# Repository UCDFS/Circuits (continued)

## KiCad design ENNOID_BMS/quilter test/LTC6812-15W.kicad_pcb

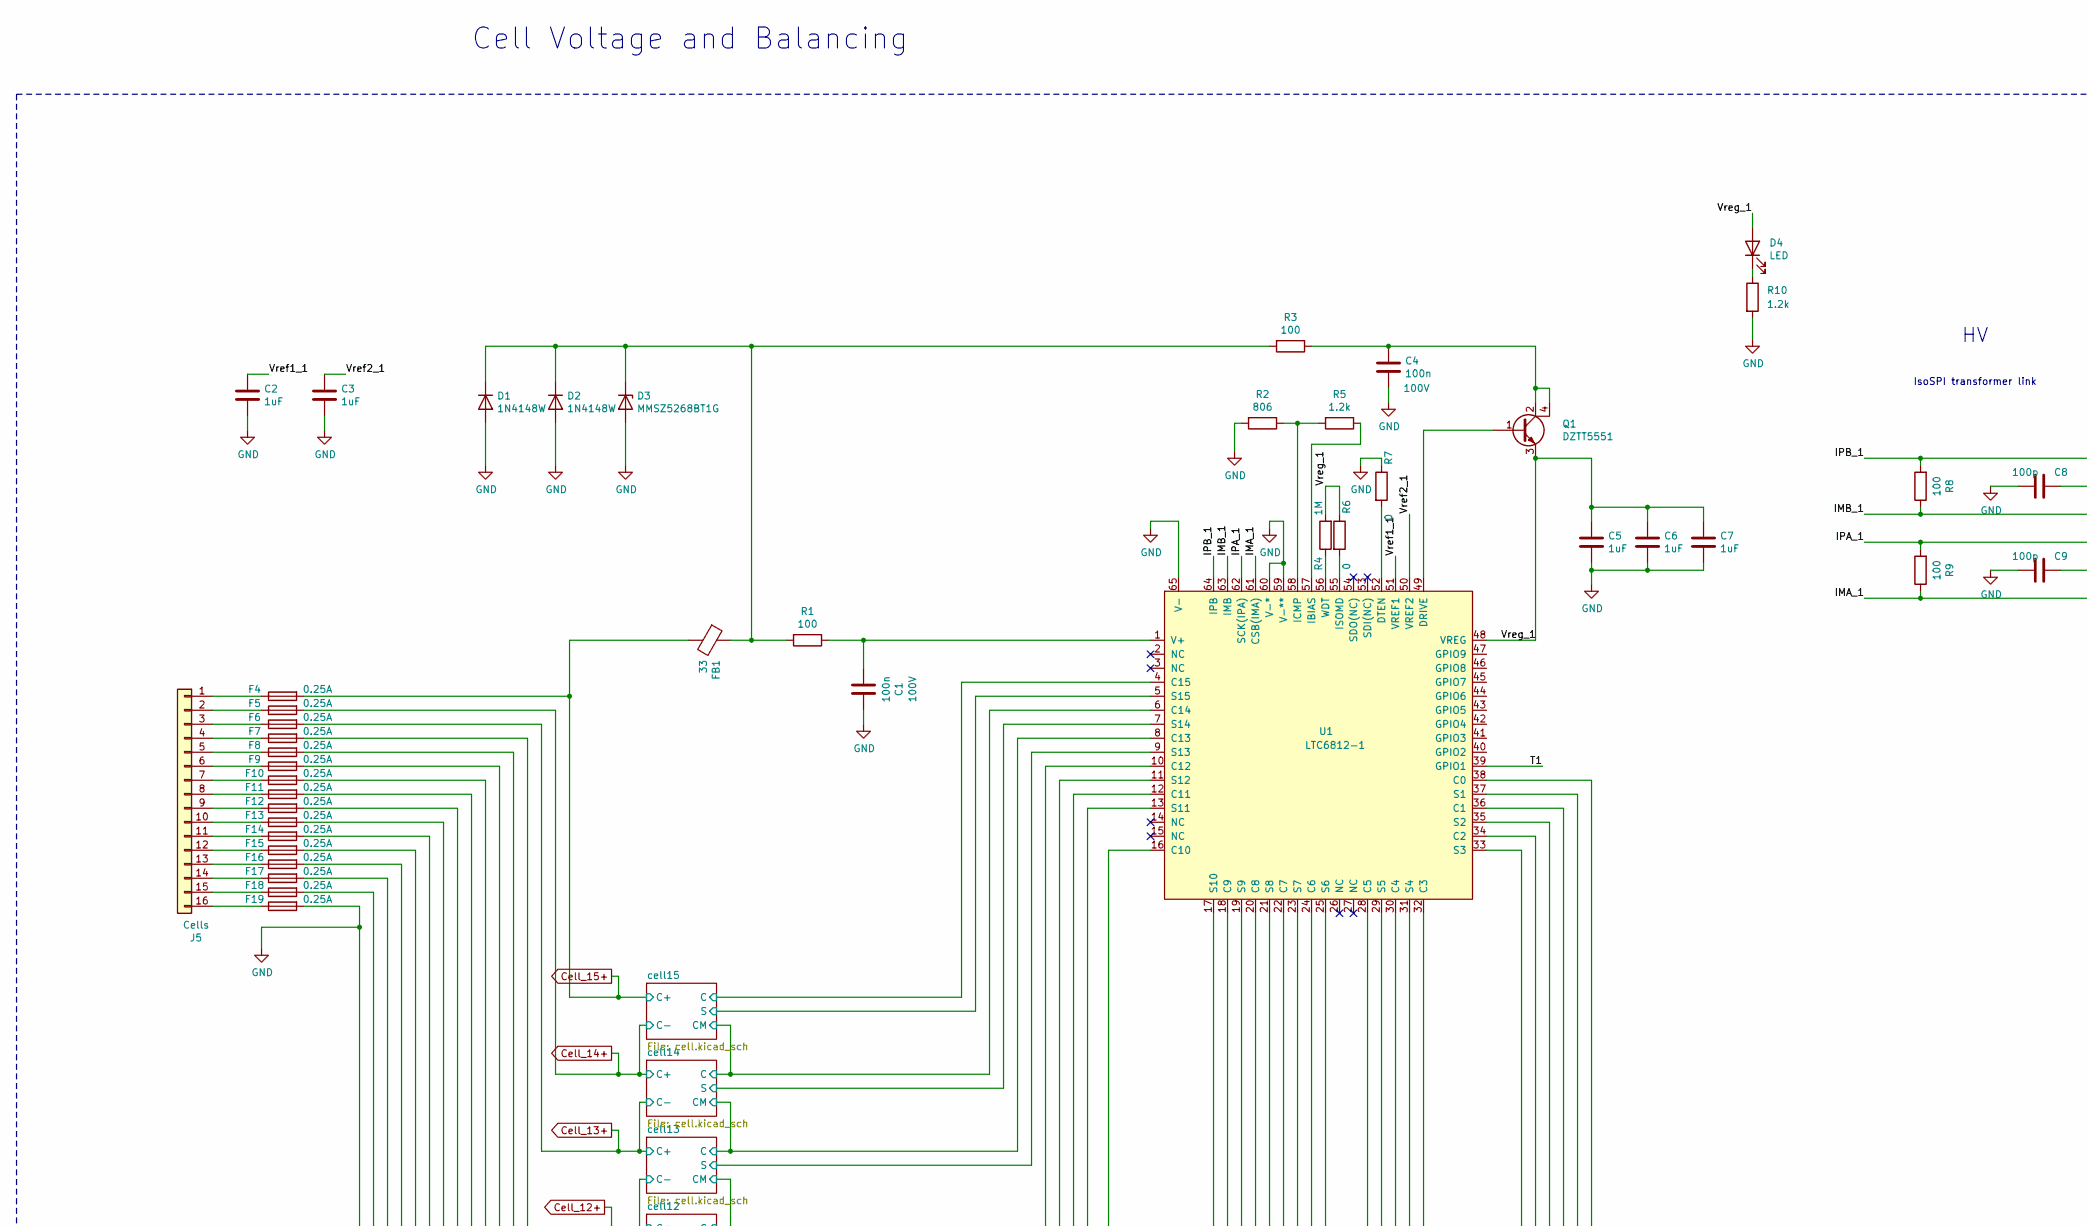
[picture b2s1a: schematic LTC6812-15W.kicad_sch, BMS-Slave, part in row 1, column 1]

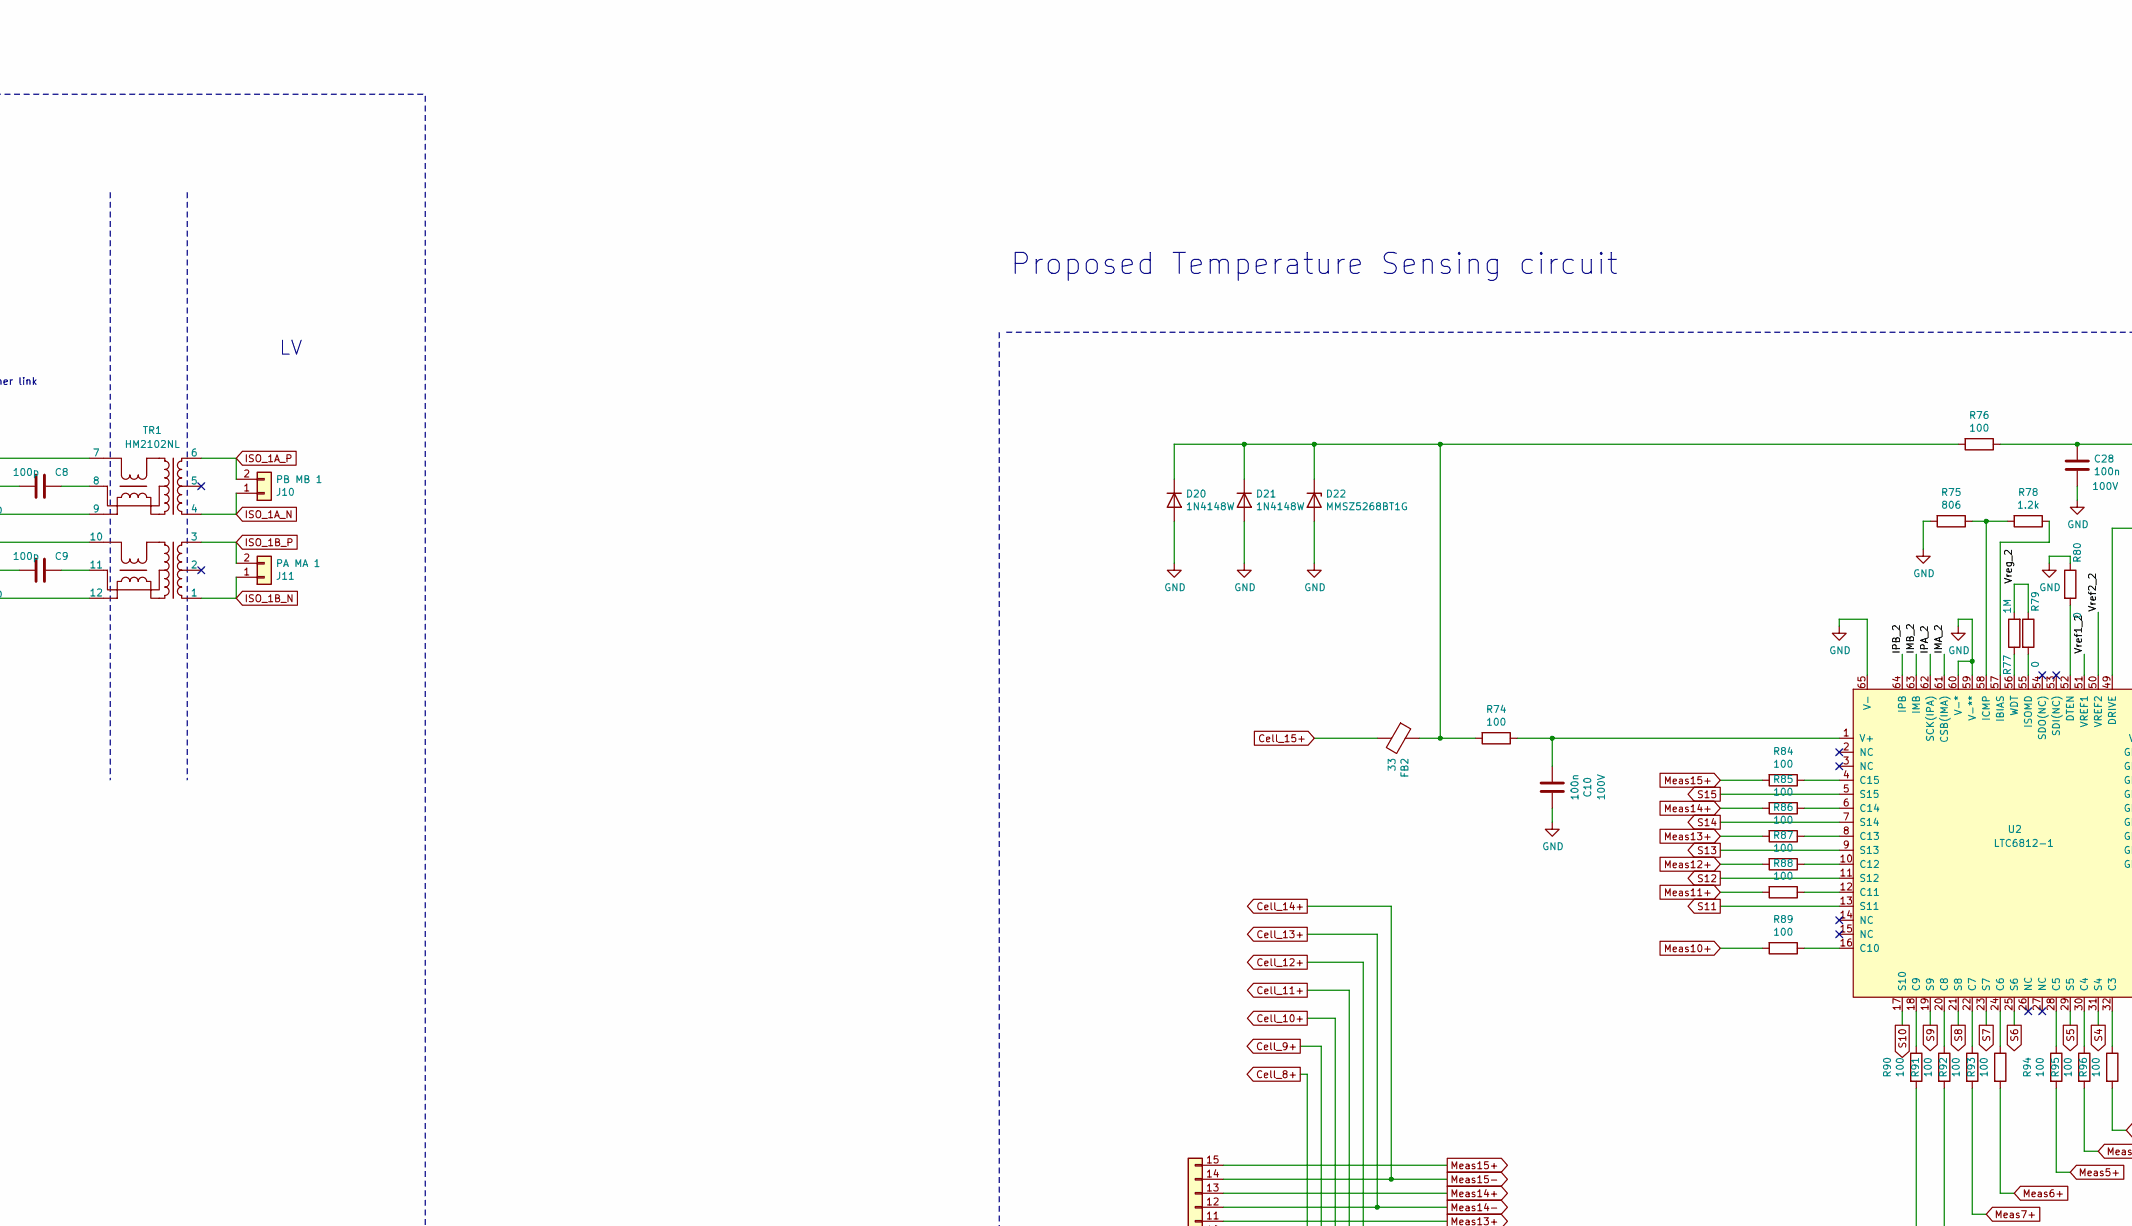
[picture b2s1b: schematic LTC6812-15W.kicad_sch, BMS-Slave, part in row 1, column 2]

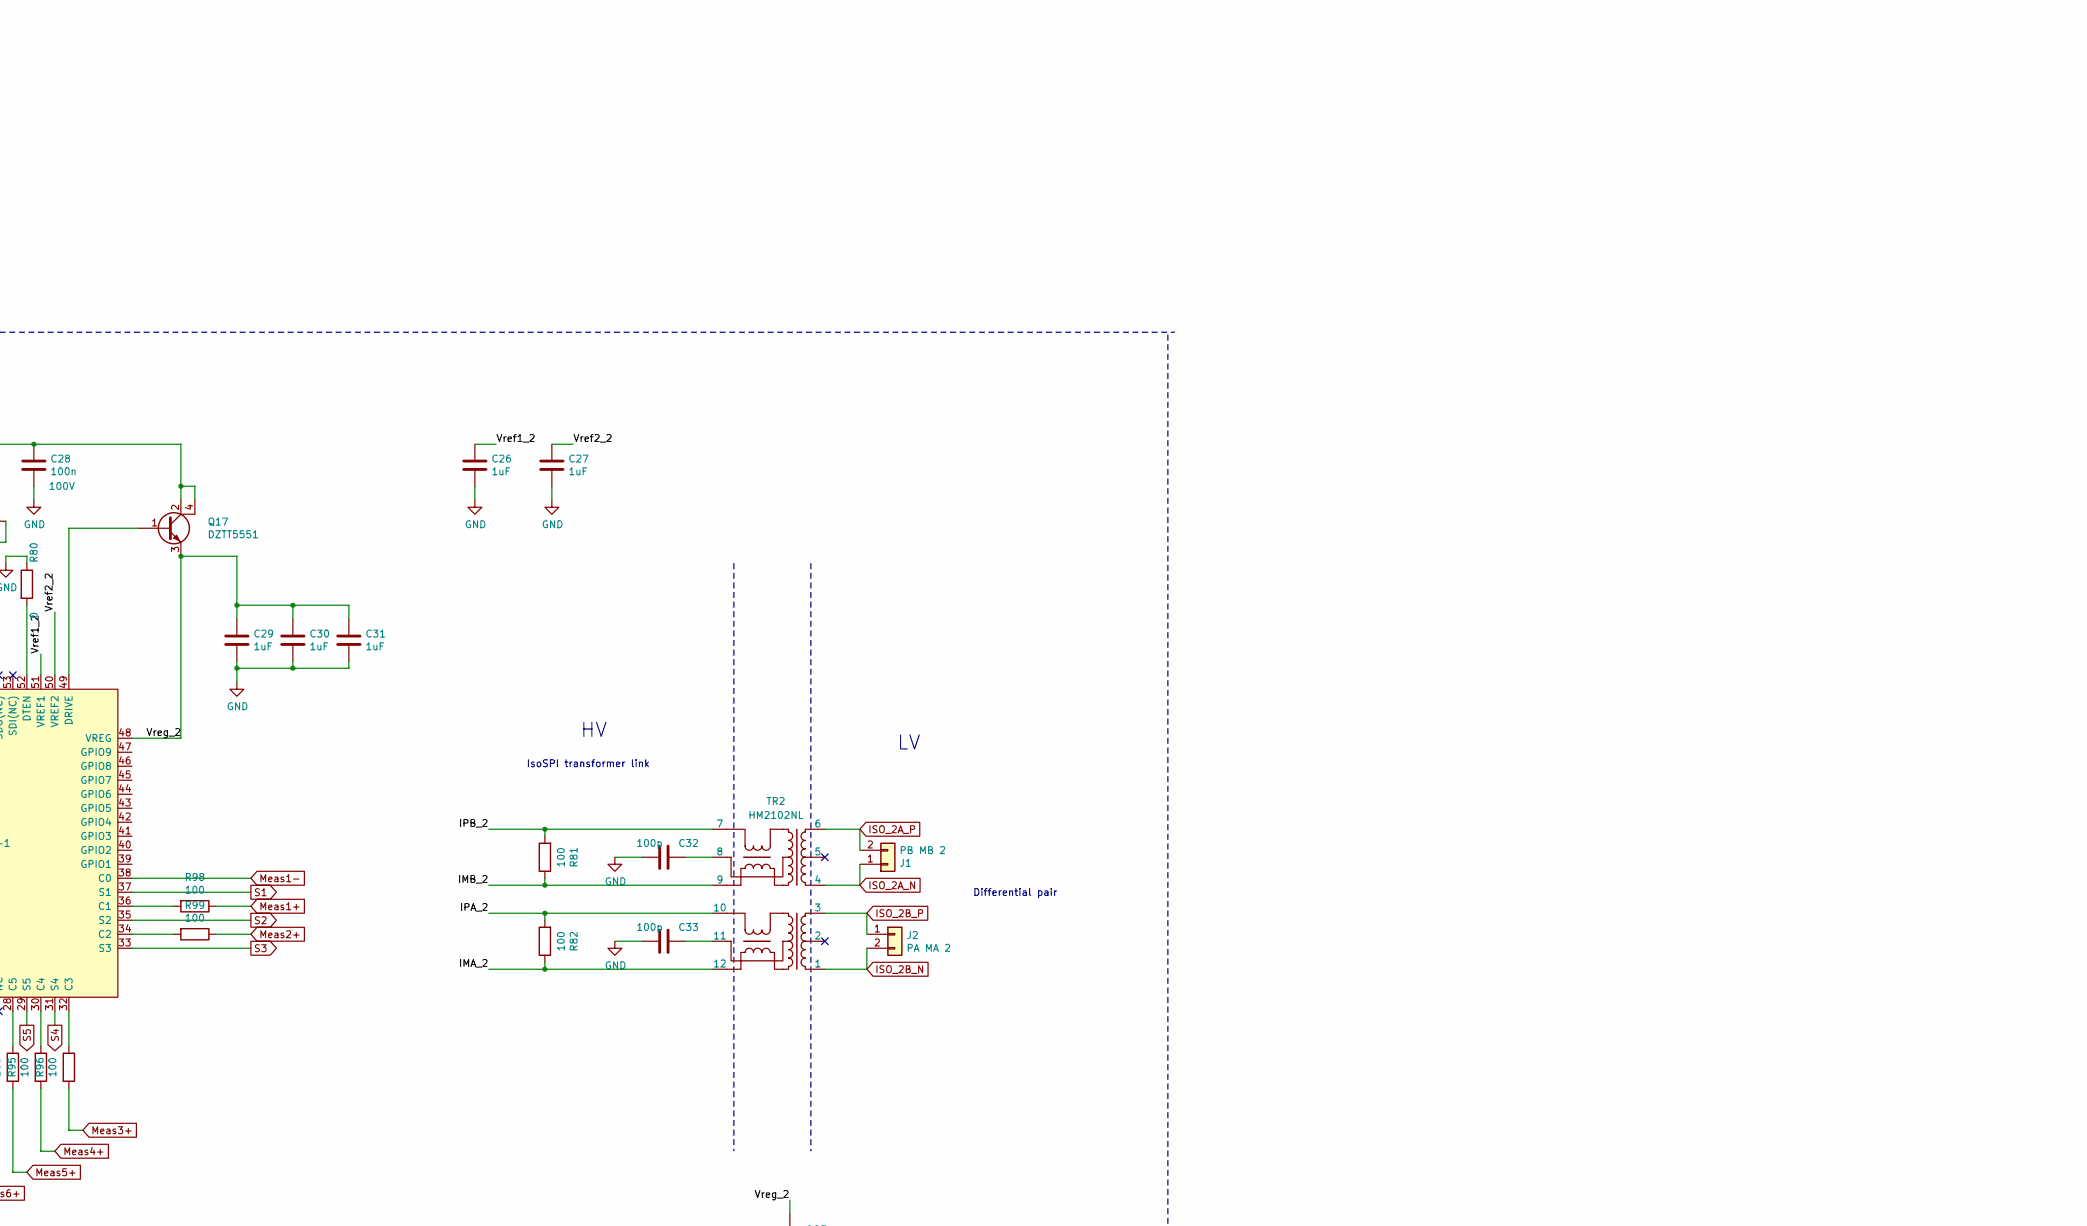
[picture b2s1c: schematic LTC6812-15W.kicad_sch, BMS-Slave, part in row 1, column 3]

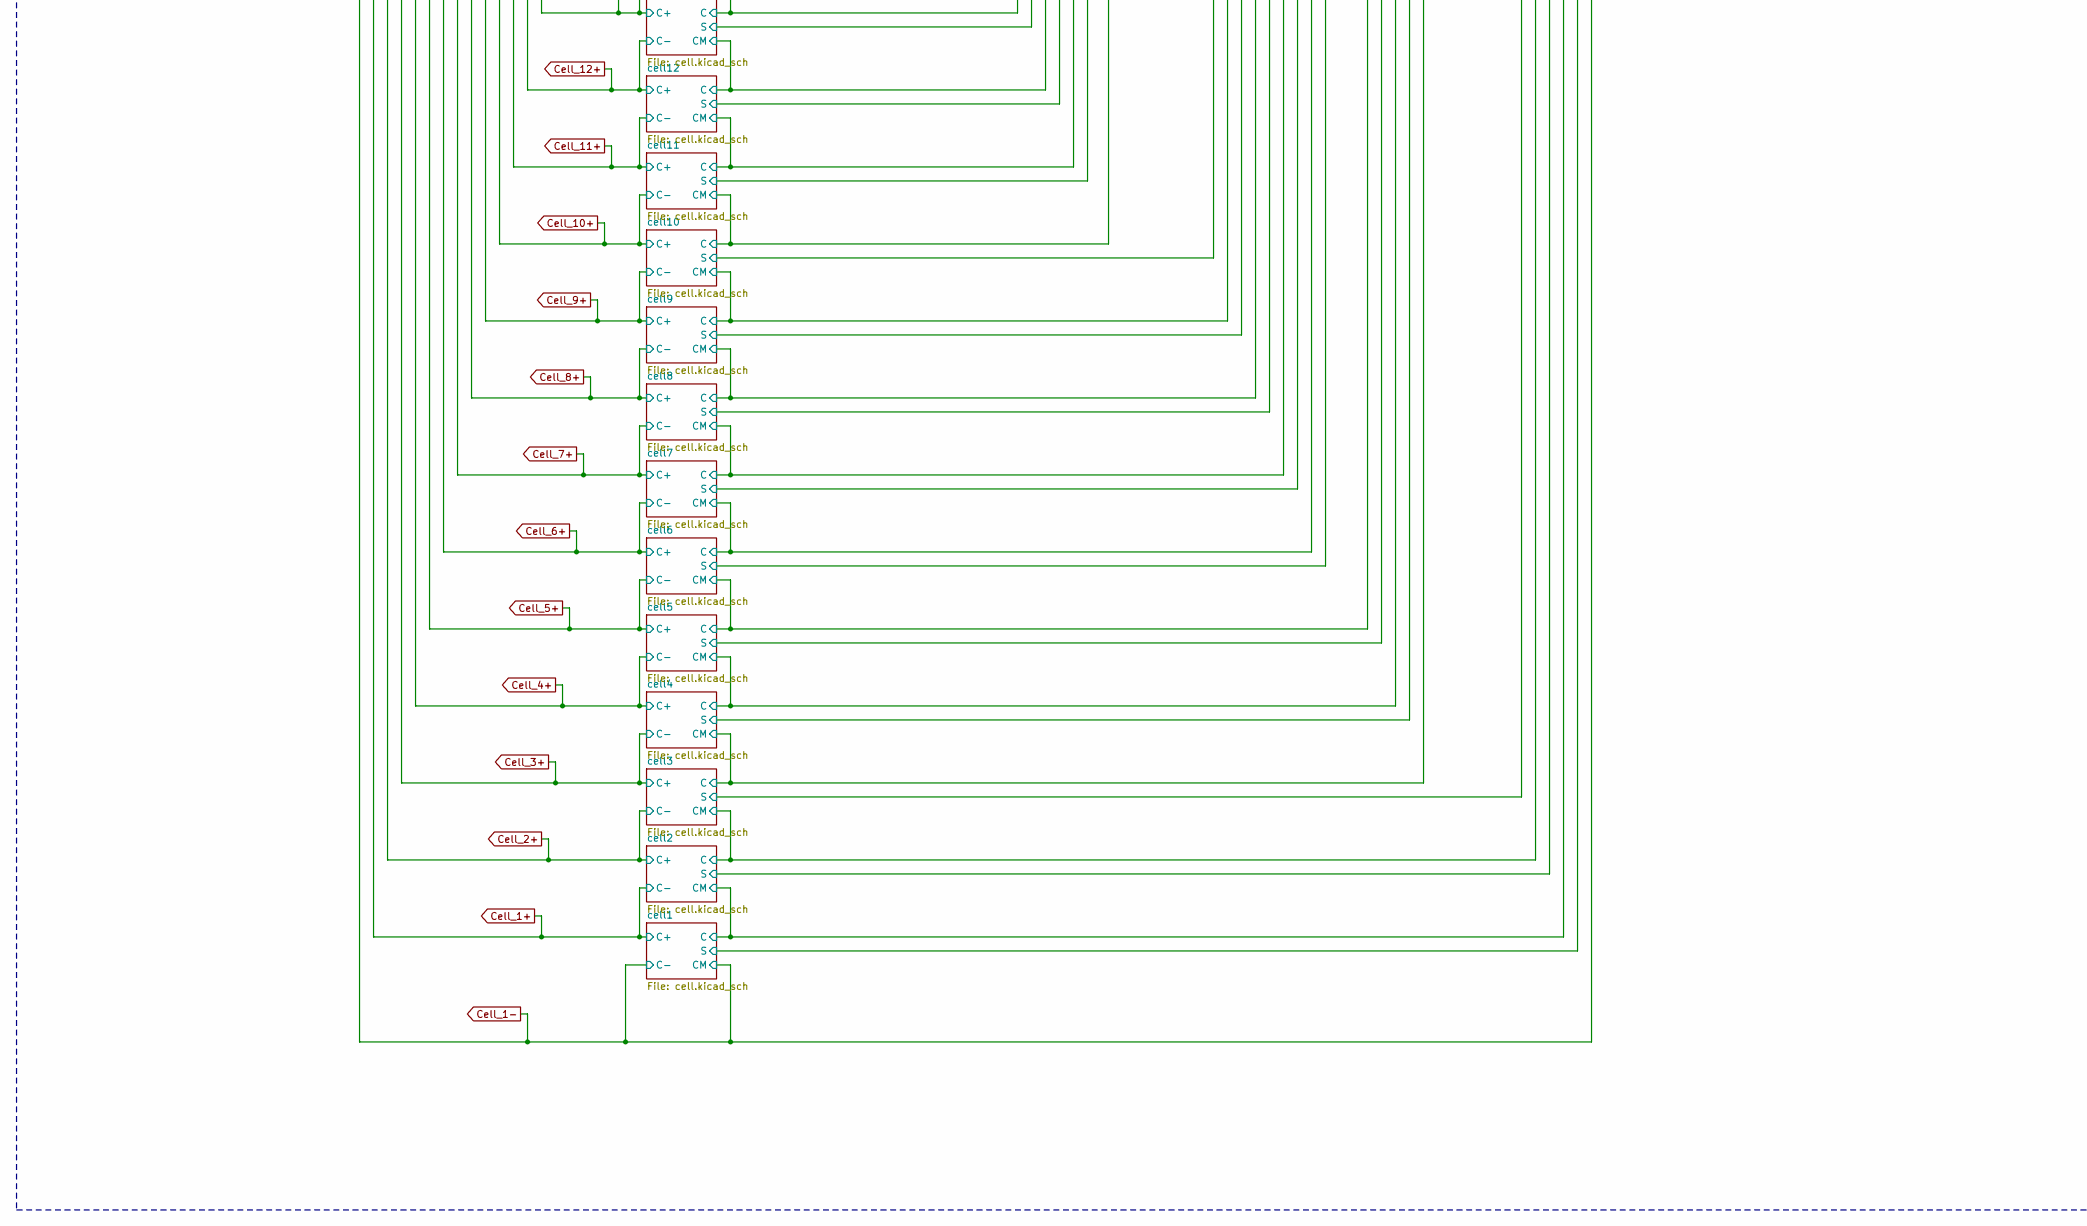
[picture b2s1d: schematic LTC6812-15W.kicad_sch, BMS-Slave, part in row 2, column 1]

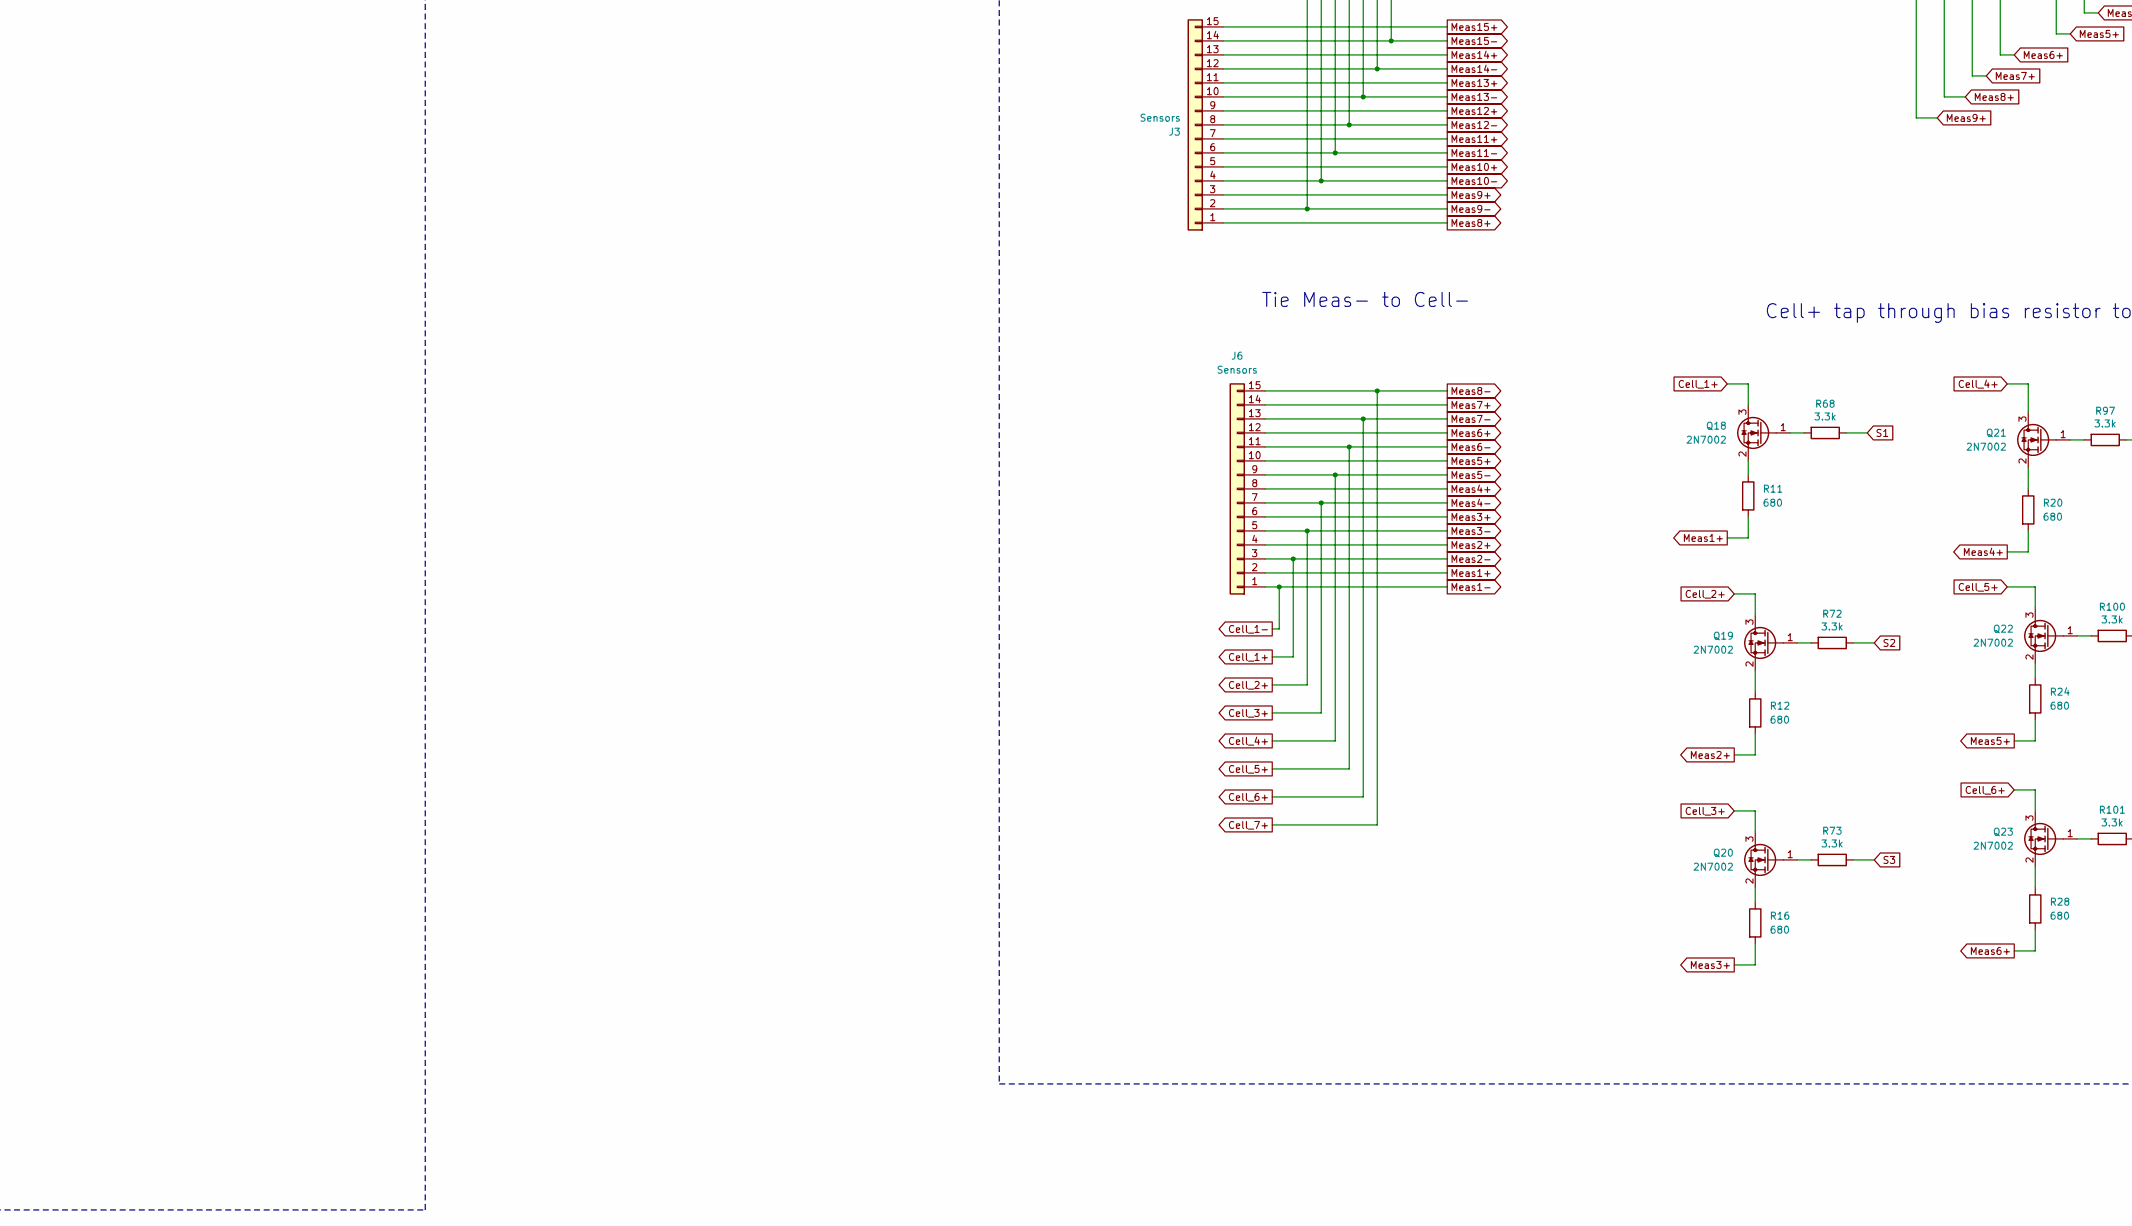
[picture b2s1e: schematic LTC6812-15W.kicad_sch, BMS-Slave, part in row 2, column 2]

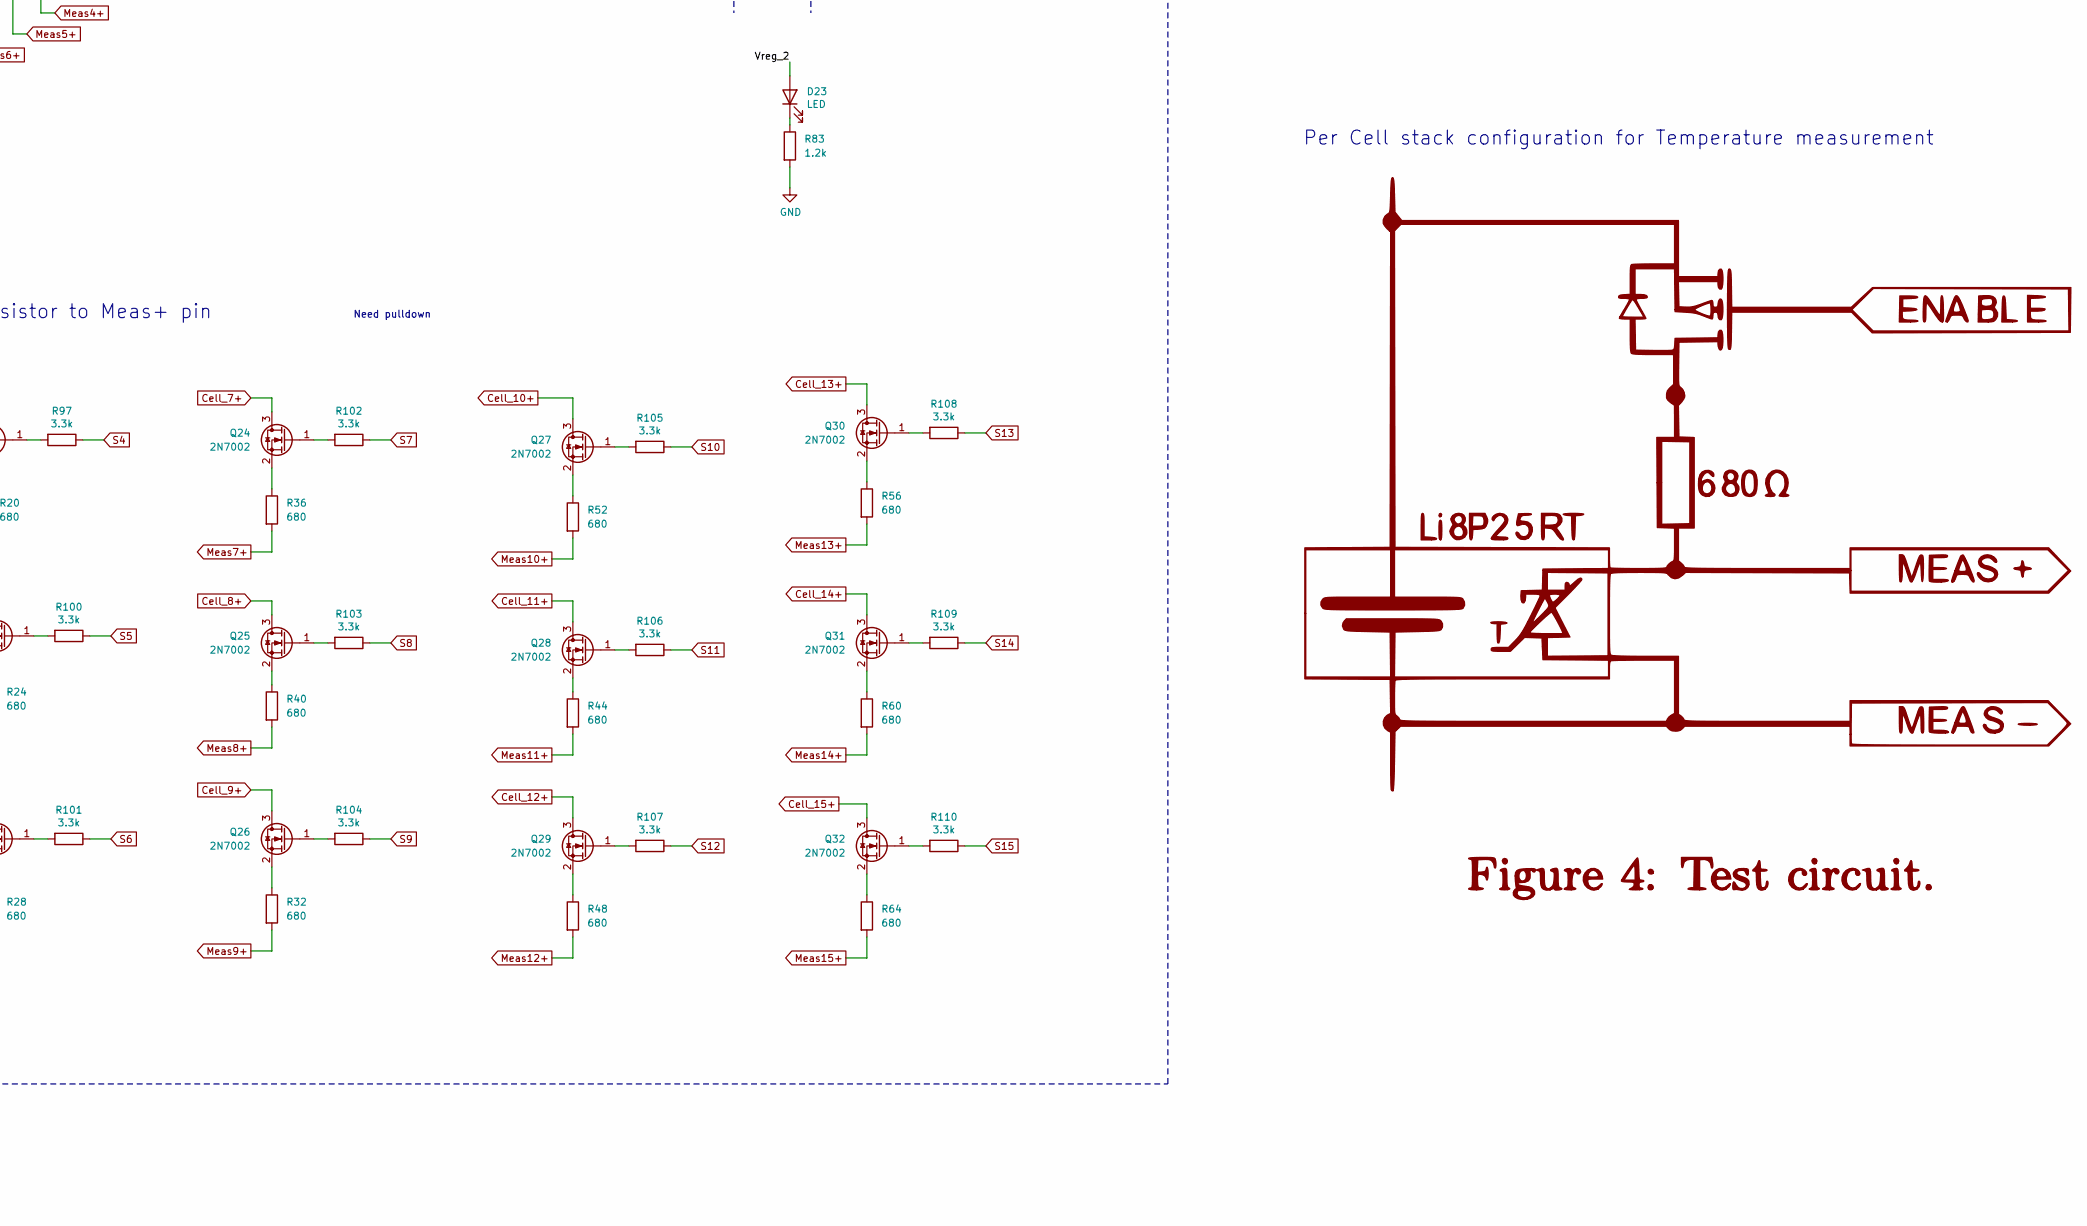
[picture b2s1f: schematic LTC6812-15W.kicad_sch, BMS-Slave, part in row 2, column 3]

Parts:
C1, C4, C10, C28: 100n; C_0603_1608Metric; Voltage 100V; Part Number GRM188R72A104KA35D
C2, C3, C5, C6, C7, C26, C27, C29, C30, C31: 1uF; C_0603_1608Metric; Part Number CL10B105KP8NNNC
C8, C9, C32, C33: 100p; C_0603_1608Metric; Part Number GRM1885C1H101JA01D
D1, D2, D20, D21: 1N4148W; D_SOD-123; Part Number 1N4148W-7-F
D3, D22: MMSZ5268BT1G; D_SOD-123; Part Number MMSZ5268BT1G
D4, D23: LED; LED_0603_1608Metric_Pad1.05x0.95mm_HandSolder; Part Number VLMTG1400-GS08
F4, F5, F6, F7, F8, F9, F10, F11, F12, F13, F14, F15, F16, F17, F18, F19: 0.25A; Fuse_0603_1608Metric; Part Number 0438.250WR
FB1, FB2: 33; R_0603_1608Metric; Part Number BLM18PG330SN1D
J1: PB MB 2; JST_XH_B2B-XH-A_1x02_P2.50mm_Vertical; Part Number B2B-XH-A
J2: PA MA 2; JST_XH_B2B-XH-A_1x02_P2.50mm_Vertical; Part Number B2B-XH-A
J3, J6: Sensors; JST_XH_S15B-XH-A_1x15_P2.50mm_Horizontal; Part Number S15B-XH-A(LF)(SN)
J5: Cells; JST_XH_S16B-XH-A_1x16_P2.50mm_Horizontal; Part Number S16B-XH-A(LF)(SN)
J10: PB MB 1; JST_XH_B2B-XH-A_1x02_P2.50mm_Vertical; Part Number B2B-XH-A
J11: PA MA 1; JST_XH_B2B-XH-A_1x02_P2.50mm_Vertical; Part Number B2B-XH-A
Q1, Q17: DZTT5551; SOT-223; Part Number DZT5551-13
Q18, Q19, Q20, Q21, Q22, Q23, Q24, Q25, Q26, Q27, Q28, Q29, Q30, Q31, Q32: 2N7002; SOT-23
R1, R3, R8, R9, R74, R76, R81, R82, R84, R85, R86, R87, R88, R89, R90, R91, R92, R93, R94, R95, R96, R98, R99: 100; R_0603_1608Metric; Part Number CRCW0603100RFKEA
R2, R75: 806; R_0603_1608Metric; Part Number CRCW0603806RFKEA
R4, R77: 1M; R_0603_1608Metric; Part Number CRCW06031M00FKEA
R5, R10, R78, R83: 1.2k; R_0603_1608Metric; Part Number CRCW06031K20FKEA
R6, R7, R79, R80: 0; R_0603_1608Metric; Part Number CRCW06030000Z0EA
R11, R12, R16, R20, R24, R28, R32, R36, R40, R44, R48, R52, R56, R60, R64: 680; R_0603_1608Metric; Part Number CRCW0603680RFKEA
R68, R72, R73, R97, R100, R101, R102, R103, R104, R105, R106, R107, R108, R109, R110: 3.3k; R_0603_1608Metric; Part Number CRCW06033K30FKEA
TR1, TR2: HM2102NL; Part Number HM2102NL
U1, U2: LTC6812-1; TQFP-64-1EP_10x10mm_P0.5mm_EP8x8mm; Part Number LTC6812-1

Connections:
/IMA_1: R9.1, TR1.12, U1.61 (CSB(IMA))
/IMA_2: R82.1, TR2.12, U2.61 (CSB(IMA))
/IMB_1: R8.1, TR1.9, U1.63 (IMB)
/IMB_2: R81.1, TR2.9, U2.63 (IMB)
/IPA_1: R9.2, TR1.10, U1.62 (SCK(IPA))
/IPA_2: R82.2, TR2.10, U2.62 (SCK(IPA))
/IPB_1: R8.2, TR1.7, U1.64 (IPB)
/IPB_2: R81.2, TR2.7, U2.64 (IPB)
/T1: U1.39 (GPIO1)
/Vref1_1: C2.2, U1.51 (VREF1)
/Vref1_2: C26.2, U2.51 (VREF1)
/Vref2_1: C3.2, U1.50 (VREF2)
/Vref2_2: C27.2, U2.50 (VREF2)
/Vreg_1: C5.2, C6.2, C7.2, D4.2 (A), Q1.3 (E), R4.2, R6.1, U1.48 (VREG)
/Vreg_2: C29.2, C30.2, C31.2, D23.2 (A), Q17.3 (E), R77.2, R79.1, U2.48 (VREG)
/cell1/C: U1.36 (C1); also elsewhere on the board
/cell1/S: U1.37 (S1); also elsewhere on the board
/cell2/C: U1.34 (C2); also elsewhere on the board
/cell2/S: U1.35 (S2); also elsewhere on the board
/cell3/C: U1.32 (C3); also elsewhere on the board
/cell3/S: U1.33 (S3); also elsewhere on the board
/cell4/C: U1.30 (C4); also elsewhere on the board
/cell4/S: U1.31 (S4); also elsewhere on the board
/cell5/C: U1.28 (C5); also elsewhere on the board
/cell5/S: U1.29 (S5); also elsewhere on the board
/cell6/C: U1.24 (C6); also elsewhere on the board
/cell6/S: U1.25 (S6); also elsewhere on the board
/cell7/C: U1.22 (C7); also elsewhere on the board
/cell7/S: U1.23 (S7); also elsewhere on the board
/cell8/C: U1.20 (C8); also elsewhere on the board
/cell8/S: U1.21 (S8); also elsewhere on the board
/cell9/S: U1.19 (S9); also elsewhere on the board
/cell10/C: U1.16 (C10); also elsewhere on the board
/cell10/CM: U1.18 (C9); also elsewhere on the board
/cell10/S: U1.17 (S10); also elsewhere on the board
/cell11/C: U1.12 (C11); also elsewhere on the board
/cell11/S: U1.13 (S11); also elsewhere on the board
/cell12/C: U1.10 (C12); also elsewhere on the board
/cell12/S: U1.11 (S12); also elsewhere on the board
/cell13/C: U1.8 (C13); also elsewhere on the board
/cell13/S: U1.9 (S13); also elsewhere on the board
/cell14/C: U1.6 (C14); also elsewhere on the board
/cell14/S: U1.7 (S14); also elsewhere on the board
/cell15/C: U1.4 (C15); also elsewhere on the board
/cell15/S: U1.5 (S15); also elsewhere on the board
Cell_1+: F18.2, J6.3, Q18.3 (D); also elsewhere on the board
Cell_1-: C1.1, C2.1, C3.1, C4.1, C5.1, C6.1, C7.1, C8.1, C9.1, C10.1, C26.1, C27.1, C28.1, C29.1, C30.1, C31.1, C32.1, C33.1, D1.2 (A), D2.2 (A), D3.2 (A), D20.2 (A), D21.2 (A), D22.2 (A), F19.2, J6.1, R2.2, R7.1, R10.2, R75.2, R80.1, R83.2, U1.38 (C0), U1.59 (V-**), U1.60 (V-*), U1.65 (V-), U2.38 (C0), U2.59 (V-**), U2.60 (V-*), U2.65 (V-); also elsewhere on the board
Cell_2+: F17.2, J6.5, Q19.3 (D); also elsewhere on the board
Cell_3+: F16.2, J6.7, Q20.3 (D); also elsewhere on the board
Cell_4+: F15.2, J6.9, Q21.3 (D); also elsewhere on the board
Cell_5+: F14.2, J6.11, Q22.3 (D); also elsewhere on the board
Cell_6+: F13.2, J6.13, Q23.3 (D); also elsewhere on the board
Cell_7+: F12.2, J6.15, Q24.3 (D); also elsewhere on the board
Cell_8+: F11.2, J3.2, Q25.3 (D); also elsewhere on the board
Cell_9+: F10.2, J3.4, Q26.3 (D); also elsewhere on the board
Cell_10+: F9.2, J3.6, Q27.3 (D); also elsewhere on the board
Cell_11+: F8.2, J3.8, Q28.3 (D); also elsewhere on the board
Cell_12+: F7.2, J3.10, Q29.3 (D); also elsewhere on the board
Cell_13+: F6.2, J3.12, Q30.3 (D); also elsewhere on the board
Cell_14+: F5.2, J3.14, Q31.3 (D); also elsewhere on the board
Cell_15+: F4.2, FB1.2, FB2.2, Q32.3 (D); also elsewhere on the board
ISO_1A_N: J10.1, TR1.4
ISO_1A_P: J10.2, TR1.6
ISO_1B_N: J11.1, TR1.1
ISO_1B_P: J11.2, TR1.3
ISO_2A_N: J1.1, TR2.4
ISO_2A_P: J1.2, TR2.6
ISO_2B_N: J2.2, TR2.1
ISO_2B_P: J2.1, TR2.3
Meas1+: J6.2, R11.2, R98.1
Meas2+: J6.4, R12.2, R99.1
Meas3+: J6.6, R16.2, R96.2
Meas4+: J6.8, R20.2, R95.2
Meas5+: J6.10, R24.2, R94.2
Meas6+: J6.12, R28.2, R93.2
Meas7+: J6.14, R36.2, R92.2
Meas8+: J3.1, R40.2, R91.2
Meas9+: J3.3, R32.2, R90.2
Meas10+: J3.5, R52.2, R89.2
Meas11+: J3.7, R44.2, R88.2
Meas12+: J3.9, R48.2, R87.2
Meas13+: J3.11, R56.2, R86.2
Meas14+: J3.13, R60.2, R85.2
Meas15+: J3.15, R64.2, R84.2
unnamed: C4.2, Q1.2 (C), Q1.4 (C), R3.1
unnamed: C8.2, TR1.8
unnamed: C9.2, TR1.11
unnamed: C28.2, Q17.2 (C), Q17.4 (C), R76.1
unnamed: C32.2, TR2.8
unnamed: C33.2, TR2.11
unnamed: D1.1 (K), D2.1 (K), D3.1 (K), FB1.1, R1.2, R3.2
unnamed: D4.1 (K), R10.1
unnamed: D20.1 (K), D21.1 (K), D22.1 (K), FB2.1, R74.2, R76.2
unnamed: D23.1 (K), R83.1
unnamed: F4.1, J5.1
unnamed: F5.1, J5.2
unnamed: F6.1, J5.3
unnamed: F7.1, J5.4
unnamed: F8.1, J5.5
unnamed: F9.1, J5.6
unnamed: F10.1, J5.7
unnamed: F11.1, J5.8
unnamed: F12.1, J5.9
unnamed: F13.1, J5.10
unnamed: F14.1, J5.11
unnamed: F15.1, J5.12
unnamed: F16.1, J5.13
unnamed: F17.1, J5.14
unnamed: F18.1, J5.15
unnamed: F19.1, J5.16
unnamed: Q1.1 (B), U1.49 (DRIVE)
unnamed: Q17.1 (B), U2.49 (DRIVE)
unnamed: Q18.1 (G), R68.2
unnamed: Q18.2 (S), R11.1
unnamed: Q19.1 (G), R72.2
unnamed: Q19.2 (S), R12.1
unnamed: Q20.1 (G), R73.2
unnamed: Q20.2 (S), R16.1
unnamed: Q21.1 (G), R97.2
unnamed: Q21.2 (S), R20.1
unnamed: Q22.1 (G), R100.2
unnamed: Q22.2 (S), R24.1
unnamed: Q23.1 (G), R101.2
unnamed: Q23.2 (S), R28.1
unnamed: Q24.1 (G), R102.2
unnamed: Q24.2 (S), R36.1
unnamed: Q25.1 (G), R103.2
unnamed: Q25.2 (S), R40.1
unnamed: Q26.1 (G), R104.2
unnamed: Q26.2 (S), R32.1
unnamed: Q27.1 (G), R105.2
unnamed: Q27.2 (S), R52.1
unnamed: Q28.1 (G), R106.2
unnamed: Q28.2 (S), R44.1
unnamed: Q29.1 (G), R107.2
unnamed: Q29.2 (S), R48.1
unnamed: Q30.1 (G), R108.2
unnamed: Q30.2 (S), R56.1
unnamed: Q31.1 (G), R109.2
unnamed: Q31.2 (S), R60.1
unnamed: Q32.1 (G), R110.2
unnamed: Q32.2 (S), R64.1
unnamed: R7.2, U1.52 (DTEN)
unnamed: R5.1, U1.57 (IBIAS)
unnamed: R2.1, R5.2, U1.58 (ICMP)
unnamed: R6.2, U1.55 (ISOMD)
unnamed: C1.2, R1.1, U1.1 (V+)
unnamed: R4.1, U1.56 (WDT)
unnamed: R98.2, U2.36 (C1)
unnamed: R99.2, U2.34 (C2)
unnamed: R96.1, U2.32 (C3)
unnamed: R95.1, U2.30 (C4)
unnamed: R94.1, U2.28 (C5)
unnamed: R93.1, U2.24 (C6)
unnamed: R92.1, U2.22 (C7)
unnamed: R91.1, U2.20 (C8)
unnamed: R90.1, U2.18 (C9)
unnamed: R89.1, U2.16 (C10)
unnamed: R88.1, U2.12 (C11)
unnamed: R87.1, U2.10 (C12)
unnamed: R86.1, U2.8 (C13)
unnamed: R85.1, U2.6 (C14)
unnamed: R84.1, U2.4 (C15)
unnamed: R80.2, U2.52 (DTEN)
unnamed: R78.1, U2.57 (IBIAS)
unnamed: R75.1, R78.2, U2.58 (ICMP)
unnamed: R79.2, U2.55 (ISOMD)
unnamed: C10.2, R74.1, U2.1 (V+)
unnamed: R77.1, U2.56 (WDT)
S1: R68.1, U2.37 (S1)
S2: R72.1, U2.35 (S2)
S3: R73.1, U2.33 (S3)
S4: R97.1, U2.31 (S4)
S5: R100.1, U2.29 (S5)
S6: R101.1, U2.25 (S6)
S7: R102.1, U2.23 (S7)
S8: R103.1, U2.21 (S8)
S9: R104.1, U2.19 (S9)
S10: R105.1, U2.17 (S10)
S11: R106.1, U2.13 (S11)
S12: R107.1, U2.11 (S12)
S13: R108.1, U2.9 (S13)
S14: R109.1, U2.7 (S14)
S15: R110.1, U2.5 (S15)

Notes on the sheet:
Differential pair
Per Cell stack configuration for Temperature measurement
Need pulldown
Cell Voltage and Balancing
Tie Meas- to Cell-
Cell+ tap through bias resistor to Meas+ pin
Proposed Temperature Sensing circuit
IsoSPI transformer link
